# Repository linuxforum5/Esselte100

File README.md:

# Esselte 100
Documentations, utilities and programs for Esselte 100 school computer

## docs
Documentations

## e100utils
Utilities for Esselte 100: bas2wav, bin2bas, wav2bas and lzss and bpe compressor.

## programs
Programs for Esselte 100. First game is Sokoban!

## remake
My Esselte 100 remake photos and KiCad files

## KiCad
KiCad files for my board and accessories

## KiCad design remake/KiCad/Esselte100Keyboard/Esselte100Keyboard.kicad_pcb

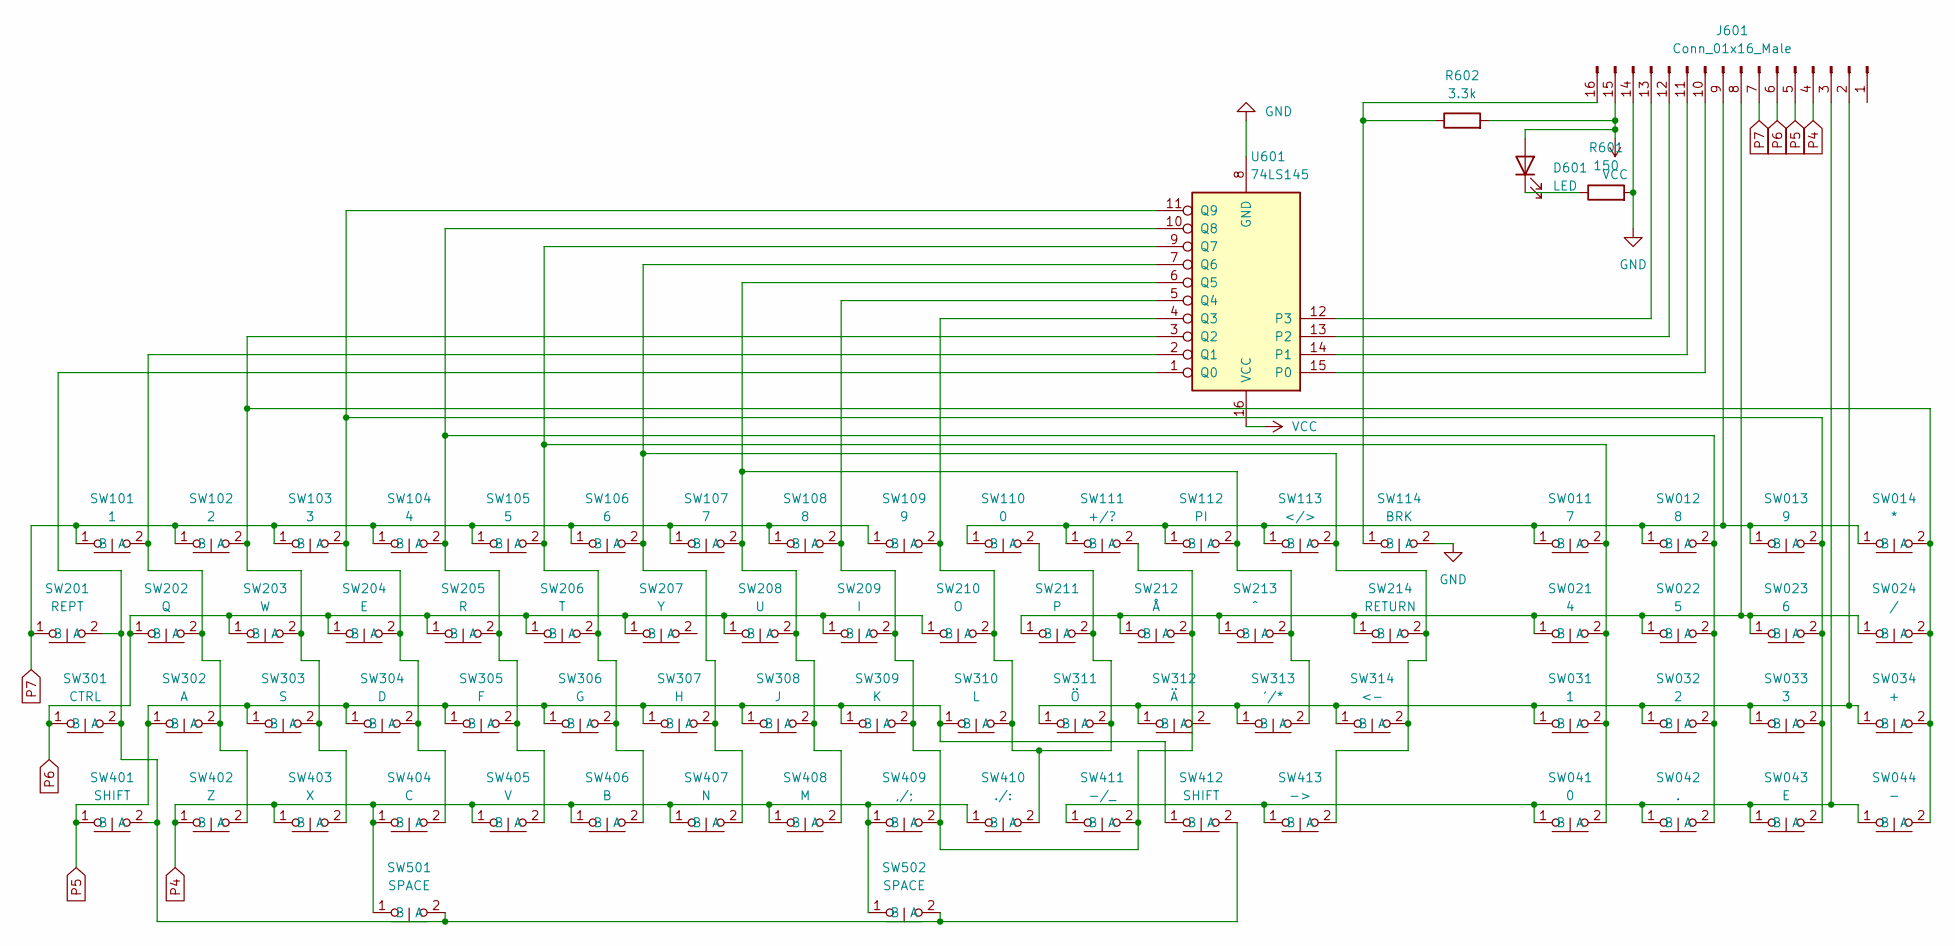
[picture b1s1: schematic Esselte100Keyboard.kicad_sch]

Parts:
D601: LED; PinSocket_1x02_P2.54mm_Vertical
J601: Conn_01x16_Male; PinSocket_1x16_P2.54mm_Vertical
R601: 150; PinSocket_1x02_P2.54mm_Vertical
R602: 3.3k; PinSocket_1x02_P2.54mm_Vertical
SW011, SW107: 7; SW_Cherry_MX_1.00u_Plate
SW012, SW108: 8; SW_Cherry_MX_1.00u_Plate
SW013, SW109: 9; SW_Cherry_MX_1.00u_Plate
SW014: *; SW_Cherry_MX_1.00u_Plate
SW021, SW104: 4; SW_Cherry_MX_1.00u_Plate
SW022, SW105: 5; SW_Cherry_MX_1.00u_Plate
SW023, SW106: 6; SW_Cherry_MX_1.00u_Plate
SW024: /; SW_Cherry_MX_1.00u_Plate
SW031, SW101: 1; SW_Cherry_MX_1.00u_Plate
SW032, SW102: 2; SW_Cherry_MX_1.00u_Plate
SW033, SW103: 3; SW_Cherry_MX_1.00u_Plate
SW034: +; SW_Cherry_MX_1.00u_Plate
SW041, SW110: 0; SW_Cherry_MX_1.00u_Plate
SW042: .; SW_Cherry_MX_1.00u_Plate
SW043, SW204: E; SW_Cherry_MX_1.00u_Plate
SW044: -; SW_Cherry_MX_1.00u_Plate
SW111: +/?; SW_Cherry_MX_1.00u_Plate
SW112: PI; SW_Cherry_MX_1.00u_Plate
SW113: </>; SW_Cherry_MX_1.00u_Plate
SW114: BRK; SW_Cherry_MX_1.00u_Plate
SW201: REPT; SW_Cherry_MX_1.00u_Plate
SW202: Q; SW_Cherry_MX_1.00u_Plate
SW203: W; SW_Cherry_MX_1.00u_Plate
SW205: R; SW_Cherry_MX_1.00u_Plate
SW206: T; SW_Cherry_MX_1.00u_Plate
SW207: Y; SW_Cherry_MX_1.00u_Plate
SW208: U; SW_Cherry_MX_1.00u_Plate
SW209: I; SW_Cherry_MX_1.00u_Plate
SW210: O; SW_Cherry_MX_1.00u_Plate
SW211: P; SW_Cherry_MX_1.00u_Plate
SW212: Å; SW_Cherry_MX_1.00u_Plate
SW213: ^; SW_Cherry_MX_1.00u_Plate
SW214: RETURN; SW_Cherry_MX_1.50u_Plate
SW301: CTRL; SW_Cherry_MX_1.00u_Plate
SW302: A; SW_Cherry_MX_1.00u_Plate
SW303: S; SW_Cherry_MX_1.00u_Plate
SW304: D; SW_Cherry_MX_1.00u_Plate
SW305: F; SW_Cherry_MX_1.00u_Plate
SW306: G; SW_Cherry_MX_1.00u_Plate
SW307: H; SW_Cherry_MX_1.00u_Plate
SW308: J; SW_Cherry_MX_1.00u_Plate
SW309: K; SW_Cherry_MX_1.00u_Plate
SW310: L; SW_Cherry_MX_1.00u_Plate
SW311: Ö; SW_Cherry_MX_1.00u_Plate
SW312: Ä; SW_Cherry_MX_1.00u_Plate
SW313: '/*; SW_Cherry_MX_1.00u_Plate
SW314: <-; SW_Cherry_MX_1.00u_Plate
SW401, SW412: SHIFT; SW_Cherry_MX_1.00u_Plate
SW402: Z; SW_Cherry_MX_1.00u_Plate
SW403: X; SW_Cherry_MX_1.00u_Plate
SW404: C; SW_Cherry_MX_1.00u_Plate
SW405: V; SW_Cherry_MX_1.00u_Plate
SW406: B; SW_Cherry_MX_1.00u_Plate
SW407: N; SW_Cherry_MX_1.00u_Plate
SW408: M; SW_Cherry_MX_1.00u_Plate
SW409: ,/;; SW_Cherry_MX_1.00u_Plate
SW410: ./:; SW_Cherry_MX_1.00u_Plate
SW411: -/_; SW_Cherry_MX_1.00u_Plate
SW413: ->; SW_Cherry_MX_1.00u_Plate
SW501, SW502: SPACE; SW_Cherry_MX_6.25u_Plate
U601: 74LS145; DIP-16_W7.62mm_LongPads

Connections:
GND: J601.14, R601.2, SW114.2 (A), U601.8 (GND)
unnamed: D601.1 (K), R601.1
unnamed: J601.2, SW031.1 (B), SW032.1 (B), SW033.1 (B), SW034.1 (B), SW311.1 (B), SW312.1 (B), SW313.1 (B), SW314.1 (B)
unnamed: J601.3, SW041.1 (B), SW042.1 (B), SW043.1 (B), SW044.1 (B), SW411.1 (B), SW413.1 (B)
unnamed: J601.8, SW021.1 (B), SW022.1 (B), SW023.1 (B), SW024.1 (B), SW211.1 (B), SW212.1 (B), SW213.1 (B), SW214.1 (B)
unnamed: J601.9, SW011.1 (B), SW012.1 (B), SW013.1 (B), SW014.1 (B), SW110.1 (B), SW111.1 (B), SW112.1 (B), SW113.1 (B)
unnamed: J601.10, U601.15 (P0)
unnamed: J601.11, U601.14 (P1)
unnamed: J601.12, U601.13 (P2)
unnamed: J601.13, U601.12 (P3)
unnamed: J601.16, R602.1, SW114.1 (B)
unnamed: SW011.2 (A), SW021.2 (A), SW031.2 (A), SW041.2 (A), SW105.2 (A), SW206.2 (A), SW306.2 (A), SW406.2 (A), U601.9 (Q7)
unnamed: SW012.2 (A), SW022.2 (A), SW032.2 (A), SW042.2 (A), SW104.2 (A), SW205.2 (A), SW305.2 (A), SW405.2 (A), U601.10 (Q8)
unnamed: SW013.2 (A), SW023.2 (A), SW033.2 (A), SW043.2 (A), SW103.2 (A), SW204.2 (A), SW304.2 (A), SW404.2 (A), U601.11 (Q9)
unnamed: SW014.2 (A), SW024.2 (A), SW034.2 (A), SW044.2 (A), SW102.2 (A), SW203.2 (A), SW303.2 (A), SW403.2 (A), U601.3 (Q2)
unnamed: SW101.2 (A), SW202.2 (A), SW302.2 (A), SW402.2 (A), U601.2 (Q1)
unnamed: SW106.2 (A), SW113.2 (A), SW214.2 (A), SW307.2 (A), SW314.2 (A), SW407.2 (A), SW413.2 (A), U601.7 (Q6)
unnamed: SW107.2 (A), SW112.2 (A), SW208.2 (A), SW213.2 (A), SW308.2 (A), SW313.2 (A), SW408.2 (A), U601.6 (Q5)
unnamed: SW108.2 (A), SW111.2 (A), SW209.2 (A), SW212.2 (A), SW309.2 (A), SW409.2 (A), SW411.2 (A), U601.5 (Q4)
unnamed: SW109.2 (A), SW110.2 (A), SW210.2 (A), SW211.2 (A), SW310.2 (A), SW311.2 (A), SW410.2 (A), U601.4 (Q3)
unnamed: SW201.2 (A), SW301.2 (A), SW401.2 (A), SW412.2 (A), SW501.2 (A), SW502.2 (A), U601.1 (Q0)
P4: J601.4, SW402.1 (B), SW403.1 (B), SW404.1 (B), SW405.1 (B), SW406.1 (B), SW407.1 (B), SW408.1 (B), SW409.1 (B), SW410.1 (B), SW501.1 (B), SW502.1 (B)
P5: J601.5, SW302.1 (B), SW303.1 (B), SW304.1 (B), SW305.1 (B), SW306.1 (B), SW307.1 (B), SW308.1 (B), SW309.1 (B), SW310.1 (B), SW401.1 (B), SW412.1 (B)
P6: J601.6, SW202.1 (B), SW203.1 (B), SW204.1 (B), SW205.1 (B), SW206.1 (B), SW207.1 (B), SW208.1 (B), SW209.1 (B), SW210.1 (B), SW301.1 (B)
P7: J601.7, SW101.1 (B), SW102.1 (B), SW103.1 (B), SW104.1 (B), SW105.1 (B), SW106.1 (B), SW107.1 (B), SW108.1 (B), SW109.1 (B), SW201.1 (B)
VCC: D601.2 (A), J601.15, R602.2, U601.16 (VCC)

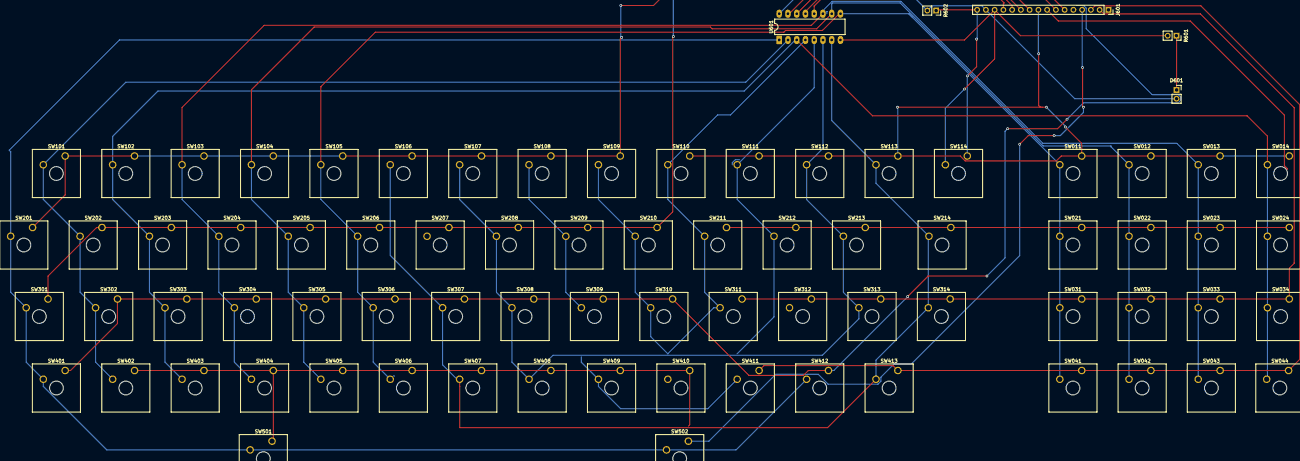
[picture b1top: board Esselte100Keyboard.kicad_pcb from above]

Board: 2 copper layers, 78 parts (0 on the bottom side), 26 nets.

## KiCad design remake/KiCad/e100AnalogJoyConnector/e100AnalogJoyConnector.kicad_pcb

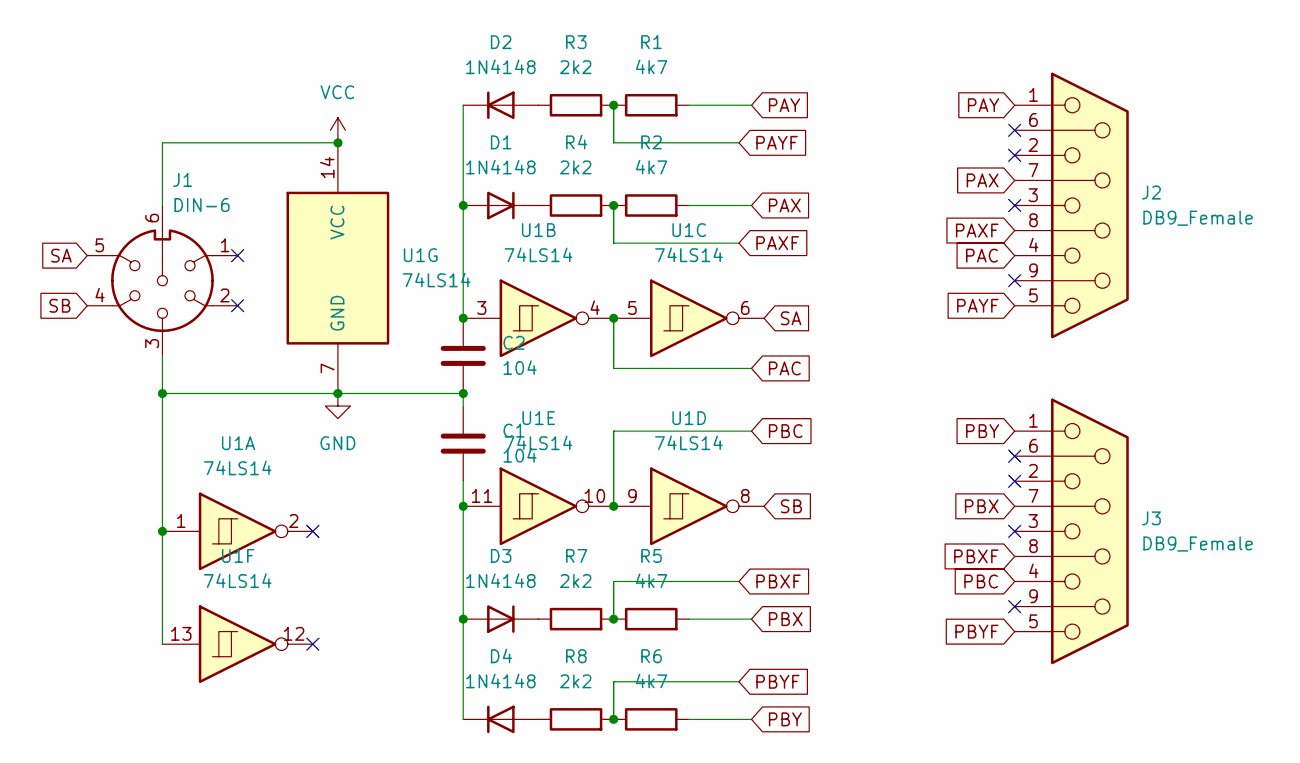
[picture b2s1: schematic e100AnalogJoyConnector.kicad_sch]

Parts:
C1, C2: 104; C_Disc_D4.3mm_W1.9mm_P5.00mm
D1, D2, D3, D4: 1N4148; D_DO-35_SOD27_P7.62mm_Horizontal
J1: DIN-6; PinSocket_1x06_P2.54mm_Vertical
J2, J3: DB9_Female; DSUB-9_Female_Horizontal_P2.77x2.54mm_EdgePinOffset9.40mm
R1, R6: 4k7; R_Axial_DIN0207_L6.3mm_D2.5mm_P10.16mm_Horizontal
R2, R5: 4k7; R_Axial_DIN0207_L6.3mm_D2.5mm_P2.54mm_Vertical
R3, R4, R7, R8: 2k2; R_Axial_DIN0207_L6.3mm_D2.5mm_P2.54mm_Vertical
U1: 74LS14; DIP-14_W7.62mm

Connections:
GND: C1.1, C2.2, J1.3, U1.1, U1.7 (GND), U1.13
unnamed: C1.2, D3.2 (A), D4.1 (K), U1.11
unnamed: C2.1, D1.2 (A), D2.1 (K), U1.3
unnamed: D3.1 (K), R7.1
unnamed: D2.2 (A), R3.1
unnamed: D1.1 (K), R4.1
unnamed: D4.2 (A), R8.1
PAC: J2.4, U1.4, U1.5
PAX: J2.7, R2.2
PAXF: J2.8, R2.1, R4.2
PAY: J2.1, R1.2
PAYF: J2.5, R1.1, R3.2
PBC: J3.4, U1.9, U1.10
PBX: J3.7, R5.2
PBXF: J3.8, R5.1, R7.2
PBY: J3.1, R6.2
PBYF: J3.5, R6.1, R8.2
SA: J1.5, U1.6
SB: J1.4, U1.8
VCC: J1.6, U1.14 (VCC)

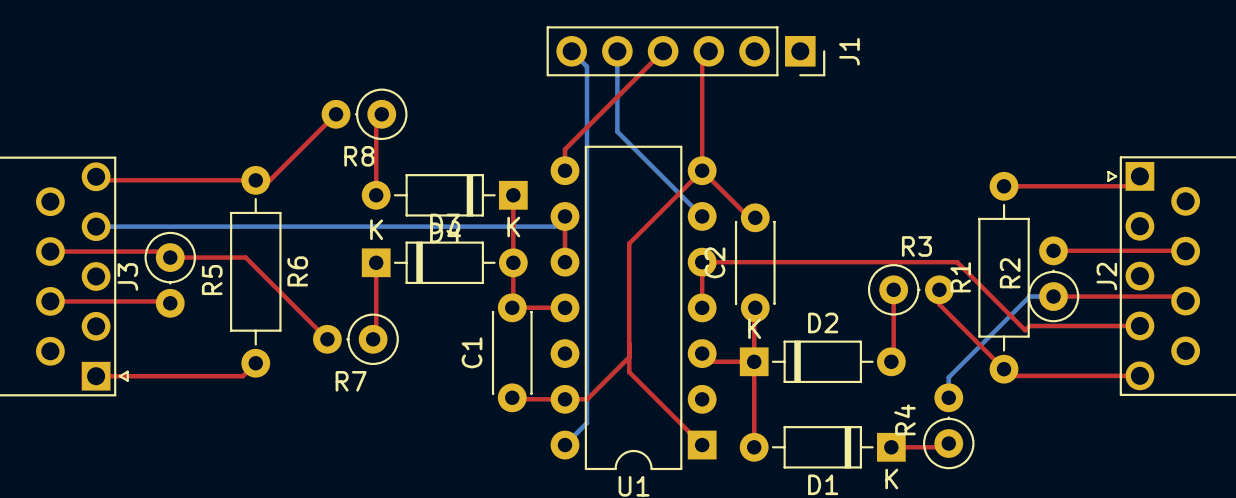
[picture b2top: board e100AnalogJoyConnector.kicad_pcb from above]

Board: 2 copper layers, 18 parts (0 on the bottom side), 20 nets.

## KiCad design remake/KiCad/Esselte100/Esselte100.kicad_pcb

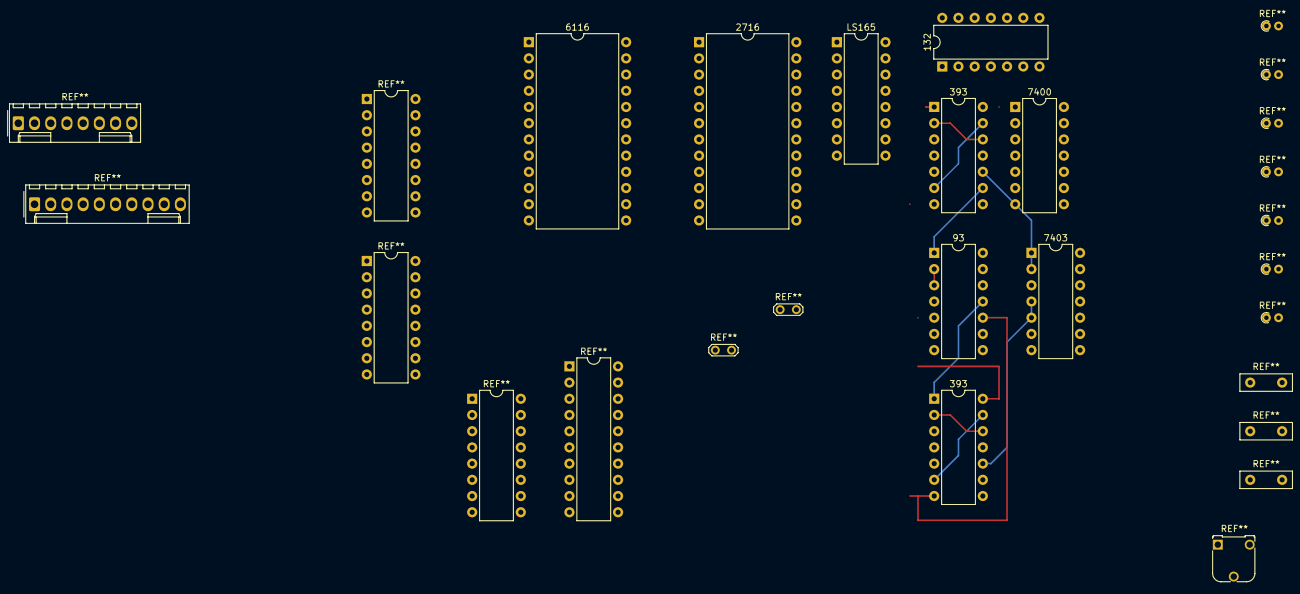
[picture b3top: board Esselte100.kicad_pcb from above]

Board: 2 copper layers, 9 parts (0 on the bottom side), 15 nets.

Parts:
93, 132, 393, 393#2, 7400, 7403: DIP-14_W7.62mm
2716, 6116: DIP-24_W15.24mm
LS165: DIP-16_W7.62mm

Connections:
GND: 93.10, 132.7, 393.7, 393#2.7, 2716.12, 7400.7, 7403.7
Q4: 2716.14, LS165.3
Q5: 2716.15, LS165.q
Q6: 2716.16, 6116.16, LS165.5
Q7: 2716.17, 6116.17, LS165.6
R3: 393#2.6, 393#2.13
R5: 393#2.10, 7403.1, 7403.2
R6: 93.9, 2716.8
R7: 93.8, 2716.7
R8: 93.11, 393.1, 2716.6
R12: 393.6, 393.13
R14: 393.10, 7403.4, 7403.5
Reset1: 93.1, 393#2.2, 393#2.9, 393#2.12
Reset2: 93.2, 93.3, 393.2, 393.12
VCC: 93.5, 132.14, 393.14, 393#2.14, 2716.24, 7400.14, 7403.14

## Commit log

2025-05-01 Doksik
2025-05-01 Fotók a hibáról
2025-06-19 Add Sokoban and utilities
2025-06-20 KiCad and photos, videos
